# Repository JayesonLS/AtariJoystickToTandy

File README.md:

# AtariJoystickToTandy

Atari to Tandy joystick adapter that fits into a D-9 shell. Designed to support Atari compatible joysticks as well as Master System and Genesis/Megadrive controllers (2 buttons only).

Public domain and provided as-is. See LICENSE for full details.

[Schematic](Schematic.pdf)

[Render of Top Side](BoardTop.png)

[Render of Bottom Side](BoardBottom.png) (R3 and R8 labels are shown backwards. Gerbers/OSHPark board have been corrected.)

[Order bare PCBs  from OSH Park](https://oshpark.com/shared_projects/tsDrmzHI)

## Parts List

* 5x 10K 0805 resistors (R1-R5)
* 4x 47K 0805 resistors (R6-R9)
* 1x 0.1uf 0805 MLCC capacitor (C1)
* 2x 1N4151W or other signal diode in SOD-124 package (D1-D2)
* 1x MC14066 or other 4066 equivalent in TSSOP 14 package (U1) 
* 1x PCB
* 30cm / 1 foot of shielded, multicore cable with at least 6 conductors.
* 1x 6 pin male DIN plug
* 1x D-9 (9 pin D-SUB) connector, of the kind with straight pins designed to be soldered to wires.
* 1x plastic shell for the D-9 connector. It must have space to enclose the PCB.
 
**Note 1:** A metal D-9 shell may be used, however extra care must be taken to avoid shorts. 
In the prototype, mylar insulation was attached to the top and bottom of the shell with double 
sided table adhesive.

**Note 2:** Soldering wires to a DIN connector can be challenging. It is possible to purchase a 
pre-soldered cable with a male 6 pin DIN connector at both ends. One cable can be cut in half
to be used for two adapters. A continuity tester may be required to determine which pins are
connected to which colored wires. These cables are typically sold as "Commodore 64 serial cables". 
For the prototype, a cable from UK eBay seller "amigakit" was used. Cables from two random 
sellers in China also appeared to be suitable. Note that none of these cables were shielded,
however no adverse affect was noted from using an unshielded cable. A cable purchased from 
UK eBay seller "retrocomputershack", while of excellent quality, was not ideal for this project
due to the way the cable shield was used for what is an analog input pin for Tandy joysticks.

## Construction Notes

This is not a simple project to construct. It is not recommended for anyone without safety knowledge and 
prior experience in assembling electronics projects.

* Clean PCB edges
  * The PCB may have small "mouse bites" or other small protrusions along the edges of the board. 
    These must be removed, such as with a file, otherwise the board will not fit inside the D-9
    shell.
  * Take appropriate health precautions for the fiberglass dust produced.
* Solder surface mount components to the PCB
  * Hot air method (gave best and quickest results with the prototype boards)
    * Apply solder paste to all resistor pads (do not apply for C1)
    * Place all resistors
    * Reflow with hot air rework station
    * Apply solder paste to pads for D1, D2 and U1
    * Place diodes and U1. Align U1 very carefully
    * Place board, resistors down, on a flat surface to hold resistors in place should they reflow in the next step. 
      For construction of the prototypes, the ground fill area of a scrap PCB was used.
    * Reflow with hot air rework station
    * Hand-solder C1 with a soldering iron
  * Soldering iron method
    * Solder resistors and capacitor
    * Solder U1
    * Solder diodes
  * Using magnification, check U1 for shorts. Small shorts may be wicked away with a dry soldering iron.
    Otherwise, use desoldering wick.
* Solder D-9 connector to PCB.
  * Place the D-9 connector into one half of the D-9 shell. The row of 4 pins should be above the row of 5 pins.
  * With the diode/U1 side of the PCB facing up, slide the PCB between the rows of pins on the D-9 connector.
  * Carefully ensure that the 4 long solder pads are lined up with with 4 pins of the D-9 connector
  * The PCB may be sagging a little at this point, this is OK, it will provide a little extra room for the
    wires fitted in a later step.
  * Solder one pin to the PCB.
  * With the iron on the one soldered pin, ensure the board is fully seated against the connector.
  * Check that pads on the board are still well aligned with the pins on the connector. Make any corrections
    now before soldering any more pins.
  * Solder the other 3 pins.
  * Flip the board/connector over and solder the 5 pins.
* Solder DIN connector to cable. 
  * No advice is given here, other than to say that it is challenging and care must be taken to avoid
    shorts or damaging the connector. Opening the connector on an existing DIN cable may be enlightening. 
    Consider purchasing one or two extra connectors to use for practice.
  * The cable shield should be attached to the DIN connector metal shell.
  * Make a note of which wire colors connector to each pin number. Looking from the solder side of the
    6 pin DIN connector, pin numbering starts at 1 and increases clockwise. The center pin is pin 6.
  * Make sure the DIN connector outer sheath is at least slid over the cable before attaching the PCB.
* Attach cable to PCB.
  * Strip approximately 35mm / 1 3/8" of the outer insulation from the PCB.
  * Trim away any usused wire colors and the shield wire back to outer insultation.
  * Strip approximately 10mm / 3/8" of insulation from each of the remaining wires.
  * For each wire, twist the strands together and tin the exposed section.
  * Cut away the tip of the exposed section of each wire to remove any frays, solder blobs, etc.
  * Insert wires into the pads on the PCB. Wires should enter from the U1 side of the board, and come
    out on the resistor side of the board. Pin 1 should be connected to pad 1, pin 2 to pad 2, etc. 
	Pad 1 is the square pad, pad 2 the next one, etc.
  * Solder the wires in place.
  * Trim the excess wire flush with the solder joints.
* Assemble the D-9 Shell
  * The wires are going to be arranged so that from the PCB, they are folded towards the D-9 connector, then
    back the other way towards the cable opening on the D-9 shell.
  * Fit the two small U-shaped strain-relief brackes over the cable.
  * Place the board assembling into one half of the shell, wires/U1 side up.
  * Check that the strain relief and wires are all in place, then fit the other side of the shell.
  * Holding the shell closed, fit one screw/nut, then the other.
  * Note that the special retention screws that may have come with the D-9 shell are not required
    for this adapter.
* Testing
  * Load up a game on the Coco.
  * Connect an Atari compatible joystick or or Sega controller, check that the direction/buttons work as expected.
  * If a voltage meter is availabe, it may pay to open the adapter D-9 shell and confirm that there is approximately
    5v fron pad 3 to pad 5. If it is significantly less than 5v, there may be a fault in the adapter.

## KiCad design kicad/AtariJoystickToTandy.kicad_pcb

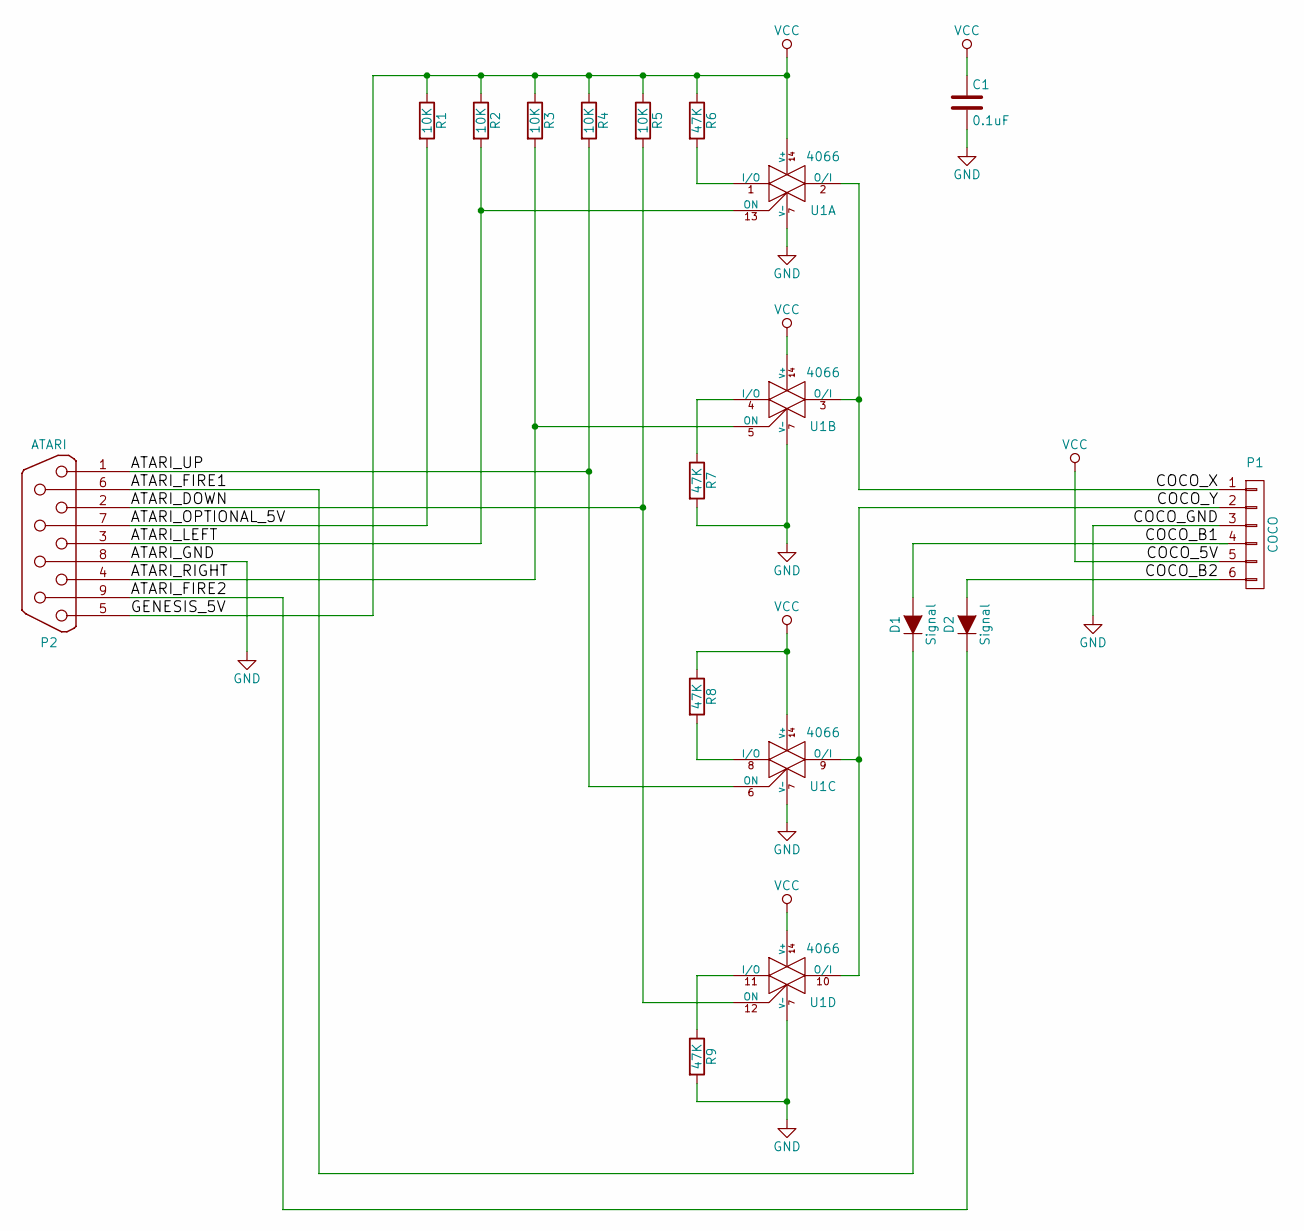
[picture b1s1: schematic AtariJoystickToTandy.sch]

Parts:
C1: 0.1uF; C_0805
D1, D2: Signal; SOD-123
P1: COCO; Pin_Header_Straight_1x07
P2: ATARI; DB9M_CI
R1, R2, R3, R4, R5: 10K; R_0805
R6, R7, R8, R9: 47K; R_0805
U1: 4066; TSSOP-14_4.4x5mm_Pitch0.65mm

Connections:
/ATARI_DOWN: P2.2, R5.2, U1.12 (ON)
/ATARI_FIRE1: D1.1 (K), P2.6
/ATARI_FIRE2: D2.1 (K), P2.9
/ATARI_LEFT: P2.3, R2.2, U1.13 (ON)
/ATARI_OPTIONAL_5V: P2.7, R1.2
/ATARI_RIGHT: P2.4, R3.2, U1.5 (ON)
/ATARI_UP: P2.1, R4.2, U1.6 (ON)
/COCO_B1: D1.2 (A), P1.4
/COCO_B2: D2.2 (A), P1.6
/COCO_X: P1.1, U1.2 (O/I), U1.3 (O/I)
/COCO_Y: P1.2, U1.9 (O/I), U1.10 (O/I)
GND: C1.2, P1.3, P2.8, R7.2, R9.2, U1.7 (V-)
unnamed: R6.2, U1.1 (I/O)
unnamed: R7.1, U1.4 (I/O)
unnamed: R8.2, U1.8 (I/O)
unnamed: R9.1, U1.11 (I/O)
VCC: C1.1, P1.5, P2.5, R1.1, R2.1, R3.1, R4.1, R5.1, R6.1, R8.1, U1.14 (V+)

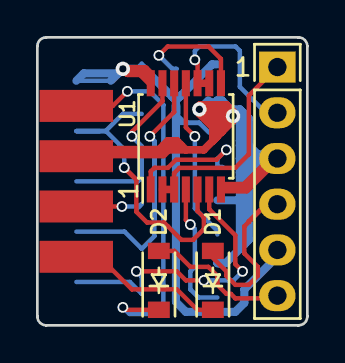
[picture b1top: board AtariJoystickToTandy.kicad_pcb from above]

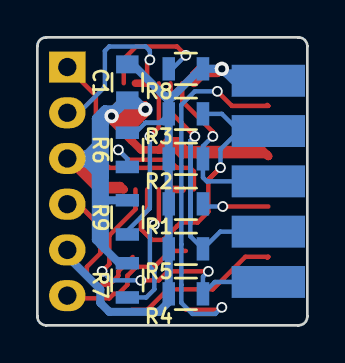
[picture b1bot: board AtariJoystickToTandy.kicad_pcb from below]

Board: 2 copper layers, 15.0 x 16.0 mm, 15 parts (11 on the bottom side), 17 nets.

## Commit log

2016-07-04 Add readme.
2016-07-04 Initial add of files.
2016-07-26 Fix incorrect locations for labels R3 and R8.
2016-07-26 Update readme to point to corrected OSHPark board.
2016-07-26 Add parts list and construction notes to readme.
2016-07-26 Add image of prototypes.
2016-07-26 Smaller image of prototypes.
2016-07-26 Add image of prototypes to readme.
2016-07-27 Add kicad files for mini-panel PCB.
